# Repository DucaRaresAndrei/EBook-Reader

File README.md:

**Duca Andrei-Rares - 331CA**

# OpenBook - E-Book Reader

## Diagrama bloc

## Descrierea functionalitatilor hardware

Proiectul OpenBook Reader se bazeaza pe un microcontroller ESP32-C6 care gestioneaza comunicatia si controlul mai multor componente si senzori. Sistemul este alimentat fie printr-un port USB-C, fie printr-o baterie Li-Po reincarcabila, gestionata de un modul de incarcare MCP73831. Tensiunea de 3.3V necesara majoritatii componentelor este furnizata de un regulator LDO.

### Module si componente principale:

- **ESP32-C6 (modul principal)**  
  Controleaza comunicatia cu toate modulele periferice prin protocoale SPI, I2C, UART si GPIO.

- **Modul de incarcare MCP73831 + baterie Li-Po**  
  Incarca acumulatorul si permite alimentarea portabila a dispozitivului.

- **LDO Voltage Regulator (XC6220A331MR-G)**  
  Stabilizeaza tensiunea la 3.3V pentru alimentarea componentelor sensibile.

- **E-Ink Display 1.5" (EPD)**  
  Afiseaza continutul static intr-un mod eficient energetic. Este controlat prin interfata SPI.

- **SD Card**  
  Utilizat pentru stocarea fisierelor, accesat prin SPI.

- **External NOR Flash 64MB (W25Q512JVEIQ)**  
  Memorie externa conectata prin SPI pentru stocare suplimentara.

- **RTC Module DS3231SN**  
  Asigura un ceas de timp real precis, comunicand prin I2C.

- **Sensor BME688**  
  Senzor ambiental (temperatura, umiditate, presiune, calitate aer) conectat prin I2C.

- **Butoane fizice (RESET, BOOT, CHANGE)**  
  Conectate direct la GPIO pentru interactiune manuala si control.

### Specificatii si interfete utilizate:

| Componenta             | Interfata       | Tensiune  | Detalii                                    |
|------------------------|-----------------|-----------|---------------------------------------------|
| E-Ink Display          | SPI             | 3.3V      | 1.5", 200x200px                             |
| SD Card                | SPI             | 3.3V      | Card microSD pentru stocare externa         |
| External NOR Flash     | SPI             | 3.3V      | Memorie Flash 64MB                          |
| RTC DS3231SN           | I2C             | 3.3V      | Ceas cu cristal integrat                    |
| Senzor BME688          | I2C             | 3.3V      | Temperatura, presiune, gaz, umiditate       |
| Butoane                | GPIO            | -         | RESET, BOOT, CHANGE                         |

### Aspecte legate de consumul de energie:

E-Ink-ul si RTC-ul sunt componente cu consum foarte redus, ceea ce permite un timp indelungat de utilizare pe baterie. Comutarea modulelor periferice se face prin pinii GPIO pentru a permite dezactivarea lor in modul deep sleep. Consumul estimat in idle este de aproximativ 0.5 mA, iar in activitate de pana la 150 mA (in functie de sarcina EPD si activitatea ESP32).

## Pini ESP32-C6

| Pin ESP32-C6 | Functie            | Componenta          | Justificare                                                                 |
|--------------|--------------------|----------------------|------------------------------------------------------------------------------|
| EN           | RESET              | Buton Reset          | Reset hardware general pentru microcontroller                               |
| IO0          | INT RTC            | RTC DS3231SN         | Semnal de wake-up de la RTC                                                 |
| IO1          | 32KHZ              | RTC DS3231SN         | Iesire frecventa 32kHz din RTC                                               |
| IO2          | MISO               | SPI (Flash, SD)      | Linie de date SPI pentru citire (shared)                                    |
| IO3          | EPD_BUSY           | E-Ink Display         | Citire stare de ocupare a display-ului                                      |
| IO4          | SS_SD              | SD Card              | Chip Select pentru cardul microSD                                           |
| IO5          | EPD_DC             | E-Ink Display         | Selectie Comanda/Data pentru e-paper                                        |
| IO6          | SCK                | SPI Bus              | Clock SPI comun pentru SD, Flash, EPD                                       |
| IO7          | MOSI               | SPI Bus              | Linie de date SPI pentru scriere (shared)                                   |
| IO8          | IO/BOOT            | Buton Boot           | Intrare in modul programare (Flash Mode)                                    |
| IO9          | -                  | -                    | Pin neutilizat                                                              |
| IO10         | -                  | -                    | Pin neutilizat                                                              |
| IO11         | FLASH_CS           | NOR Flash            | Chip Select dedicat pentru memoria externa                                  |
| IO12         | USB D-             | USB-C                | Linie USB pentru comunicare si alimentare                                   |
| IO13         | USB D+             | USB-C                | Linie USB pentru comunicare si alimentare                                   |
| IO15         | IO/CHANGE          | Buton CHANGE         | Buton pentru schimbarea modului de afisare sau functionalitate              |
| IO16         | TX (UART0)         | Debug Serial         | Transmitere date catre monitor serial                                       |
| IO17         | RX (UART0)         | Debug Serial         | Receptie date de la monitor serial                                          |
| IO18         | RTC_RST            | RTC DS3231SN         | Reset software pentru RTC                                                   |
| IO19         | I2C_PW             | BME688               | Control alimentare senzor prin tranzistor                                   |
| IO20         | EPD_3V3_C          | E-Ink Display         | Activare alimentare 3.3V pentru e-paper                                     |
| IO21         | SDA                | I2C (RTC, BME688)    | Linia de date I2C partajata                                                 |
| IO22         | SCL                | I2C (RTC, BME688)    | Linia de ceas I2C partajata                                                 |
| IO23         | EPD_RST            | E-Ink Display         | Reset hardware pentru display                                               |

## Bill Of Materials

| Componenta | Link de cumparare | Datasheet |
|-----------|--------------|-----------|
| ESP32-C6-WROOM-1-N8 | [Model](https://www.snapeda.com/parts/ESP32-C6-WROOM-1-N8/Espressif+Systems/view-part/?ref=eda) | [Datasheet](//efaidnbmnnnibpcajpcglclefindmkaj/https://www.mouser.com/catalog/specsheets/Espressif_ESP32_C6_WROOM_1%20_Datasheet_V0.1_PRELIMINARY_en.pdf?srsltid=AfmBOooHQKNitqODRaaPjoZInfWKTacDER1t5uRK6sKqT13TrzvVo_B7) |
| Si1308EDL-T1-GE3 | [Model](https://componentsearchengine.com/part-view/SI1308EDL-T1-GE3/Vishay) | [Datasheet](https://www.alldatasheet.com/view.jsp?Searchword=Si1308edl&gad_source=1&gbraid=0AAAAADcdDU-px713ONYSnQ2O-gcwqYcFq&gclid=Cj0KCQjwqcO_BhDaARIsACz62vN_Nz3MJOc6J_03gnVBm7aSqC8v9wyP0VD-iRKP-gFrYgdhLi99I14aAlVJEALw_wcB) |
| KP-1608SURCK | [Model](https://www.snapeda.com/parts/KP-1608SURCK/Kingbright/view-part/?ref=search&t=LED%200603) | [Datasheet](//efaidnbmnnnibpcajpcglclefindmkaj/https://media.elv.com/file/107153_led_surck1608_data.pdf) |
| R0402 | [Model](https://componentsearchengine.com/part-view/R0402%201%25%20100%20K%20(RC0402FR-07100KL)/YAGEO) | [Datasheet](//efaidnbmnnnibpcajpcglclefindmkaj/https://www.resistor.com/assets/pdf/0402tstd.pdf) |
| DS3231SN# | [Model](https://www.snapeda.com/parts/DS3231SN%23/Analog+Devices/view-part/?ref=eda) | [Datasheet](https://www.alldatasheet.com/view.jsp?Searchword=Ds3231sn%20datasheet&gad_source=1&gbraid=0AAAAADcdDU-Gy9URfMxGmqiPg7ci5L3wR&gclid=Cj0KCQjwqcO_BhDaARIsACz62vMkK3ETSnW2w7mo0Fa-wgWJGn89AxWCyIND6k5X8MmoPl6hv6VWwT8aAiS-EALw_wcB) |
| PGB1010603MR | [Model](https://www.snapeda.com/parts/PGB1010603MR/Littelfuse/view-part/?ref=eda) | [Datasheet](https://www.alldatasheet.com/view.jsp?Searchword=Pgb1010603mr&gad_source=1&gbraid=0AAAAADcdDU8aYfZtfJfdZ9I5j6RwZ_cbA&gclid=Cj0KCQjwqcO_BhDaARIsACz62vOPBOBe0eOh5gDUFkkKl4JBcbmoFZYtJ8BOnbaWqr_BuUCcVWvbutAaAmGkEALw_wcB) |
| USBLC6-2SC6Y | [Model](https://www.snapeda.com/parts/USBLC6-2SC6Y/STMicroelectronics/view-part/?ref=eda) | [Datasheet](https://www.digikey.com/en/htmldatasheets/production/1375342/0/0/1/usblc6-2sc6y) |
| USB4110-GF-A | [Model](https://componentsearchengine.com/part-view/USB4110-GF-A/GCT%20(GLOBAL%20CONNECTOR%20TECHNOLOGY)) | [Datasheet](//efaidnbmnnnibpcajpcglclefindmkaj/https://gct.co/files/drawings/usb4110.pdf) |
| CPH3225A | [Model](https://www.snapeda.com/parts/CPH3225A/Seiko+Instruments/view-part/?ref=eda) | [Datasheet](https://octopart.com/datasheet/cph3225a-seiko-25340571) |
| Adafruit | [Model](https://eu.mouser.com/ProductDetail/Adafruit/4208?qs=PzGy0jfpSMtbScLbr0L5dw%3D%3D) | [Datasheet](https://www.arrow.com/en/manufacturers/adafruit-industries/datasheets) |
| SD0805S020S1R0 | [Model](https://ro.mouser.com/ProductDetail/KYOCERA-AVX/SD0805S020S1R0?qs=jCA%252BPfw4LHbpkAoSnwrdjw%3D%3D) | [Datasheet](https://www.alldatasheet.com/view.jsp?Searchword=SD0805S&sField=2) |
| W25Q512JVEIQ | [Model](https://www.snapeda.com/parts/ESP32-C6-WROOM-1-N8/Espressif+Systems/view-part/?ref=eda) | [Datasheet](//efaidnbmnnnibpcajpcglclefindmkaj/https://www.mouser.com/datasheet/2/949/W25Q512JV_SPI_RevB_06252019_KMS-2487502.pdf?srsltid=AfmBOoquExqDVgxEELF9CzuOGxHos0CD1nQDROHD6Eebdm2foNzqozqU) |
| EVQPUJ02K | [Model](https://industry.panasonic.com/global/en/products/control/switch/light-touch/number/evqpuj02k) | [Datasheet](https://www.lcsc.com/datasheet/lcsc_datasheet_2201121800_PANASONIC-EVQPUJ02K_C2936858.pdf) |
| XC6220A331MR-G | [Model](https://componentsearchengine.com/part-view/XC6220A331MR-G/Torex) | [Datasheet](https://www.alldatasheet.com/view.jsp?Searchword=Xc6220&gad_source=1&gbraid=0AAAAADcdDU8aYfZtfJfdZ9I5j6RwZ_cbA&gclid=Cj0KCQjwqcO_BhDaARIsACz62vPS06NB6tLgniZzfaVpKNu1m811BNk6AEPfg4DbP6f5S8QWA_pW_UQaAv-0EALw_wcB) |
| Bobina | [Model](https://store.comet.srl.ro/Catalogue/Product/43497/) | [Datasheet](https://www.scribd.com/document/814581278/Datasheet-Bobina) |
| MAX17048G+T10 | [Model](https://www.snapeda.com/parts/MAX17048G+T10/Analog+Devices/view-part/?ref=eda) | [Datasheet](https://www.alldatasheet.com/view.jsp?Searchword=Max17048&gad_source=1&gbraid=0AAAAADcdDU8aYfZtfJfdZ9I5j6RwZ_cbA&gclid=Cj0KCQjwqcO_BhDaARIsACz62vNa9xrVfzjCjADRwXD0RBbo4Nret3ywwteDGLJKZui8ZL8KdVlTE7caAvQxEALw_wcB) |
| SMD Solder | [Model](https://grabcad.com/library/solder-jumpers-1) | [Datasheet]() |
| BUTTON | [Model](https://industry.panasonic.com/global/en/products/control/switch/light-touch/number/evqpuj02k) | [Datasheet](https://www.lcsc.com/datasheet/lcsc_datasheet_2201121800_PANASONIC-EVQPUJ02K_C2936858.pdf) |
| BME680 | [Model](https://www.snapeda.com/parts/BME680/Bosch/view-part/?welcome=home) | [Datasheet](//efaidnbmnnnibpcajpcglclefindmkaj/https://www.bosch-sensortec.com/media/boschsensortec/downloads/datasheets/bst-bme680-ds001.pdf) |
| PFMF | [Model](https://www.mouser.co.uk/ProductDetail/EPCOS-TDK/B72520T0350K062?qs=dEfas%2FXlABIszF52uu7vrg%3D%3D) | [Datasheet](https://ro.mouser.com/c/ds/circuit-protection/thermistors/resettable-fuses-pptc/?m=Schurter&series=PFMF) |
| DMG2305UX-7 | [Model](https://componentsearchengine.com/part-view/DMG2305UX-7/Diodes%20Incorporated) | [Datasheet](//efaidnbmnnnibpcajpcglclefindmkaj/https://www.mouser.com/datasheet/2/115/DMG2305UX-266242.pdf?srsltid=AfmBOop22k34YTJJra1xubiU6LPiN4M4JlcWbRoSNdxSGFak8uWgXPpK) |
| BD5229G-TR | [Model](https://componentsearchengine.com/part-view/BD5229G-TR/ROHM%20Semiconductor) | [Datasheet](https://www.lcsc.com/datasheet/lcsc_datasheet_2201131330_ROHM-Semicon-BD5229G-TR_C962636.pdf) |
| MCP73831T-5ACI/OT | [Model](https://www.mouser.co.uk/ProductDetail/Microchip-Technology/MCP73831T-5ACI-OT?qs=hH%252BOa0VZEiAcgAcEkuamXg%3D%3D) | [Datasheet](//efaidnbmnnnibpcajpcglclefindmkaj/https://ww1.microchip.com/downloads/en/DeviceDoc/MCP73831-Family-Data-Sheet-DS20001984H.pdf) |
| CAPACITOR | [Model](https://componentsearchengine.com/part-view/R0402%201%25%20100%20K%20(RC0402FR-07100KL)/YAGEO) | [Datasheet](//efaidnbmnnnibpcajpcglclefindmkaj/https://www.resistor.com/assets/pdf/0402tstd.pdf) |

## Etapele implementarii proiectului:

- Am realizat schematicul conform exemplului din cerinta si folosind biblioteca specificata. Am verificat cu ERC si nu am intampinat nicio eroare. Warningurile avute au fost acceptate deoarece nu reprezinta o problema pentru structura proiectului.

- Am proiectat PCb-ul, unde am respectat in clar dimensiunile date. Am pozitionat cu grija piesele, incercand sa le pozitionez ca in fisierul exemplu. Am facut rutarea, planurile de masa si am rulat cu fisierul corect de DRC. Am rezolvat erorile de air wire pe cat de mult posibil, ramanand doar una, ce am fost nevoit sa o accept.

- Am modelat piesele 3D si le-am integrat in placa. Am intampinat probleme in a gasi anumite modele 3D, ba chiar am fost nevoit sa creez singur test pad-urile.

- Am creat manual bateria si displayul, dupa masuratorile si specificatiile cerute si le-am atasat, alaturi de modelul 3d al PCB-ului, la carcasa eBook-Reader-ului.

- Am corectat erorile, iar acum proiectul poate fi complet functional.

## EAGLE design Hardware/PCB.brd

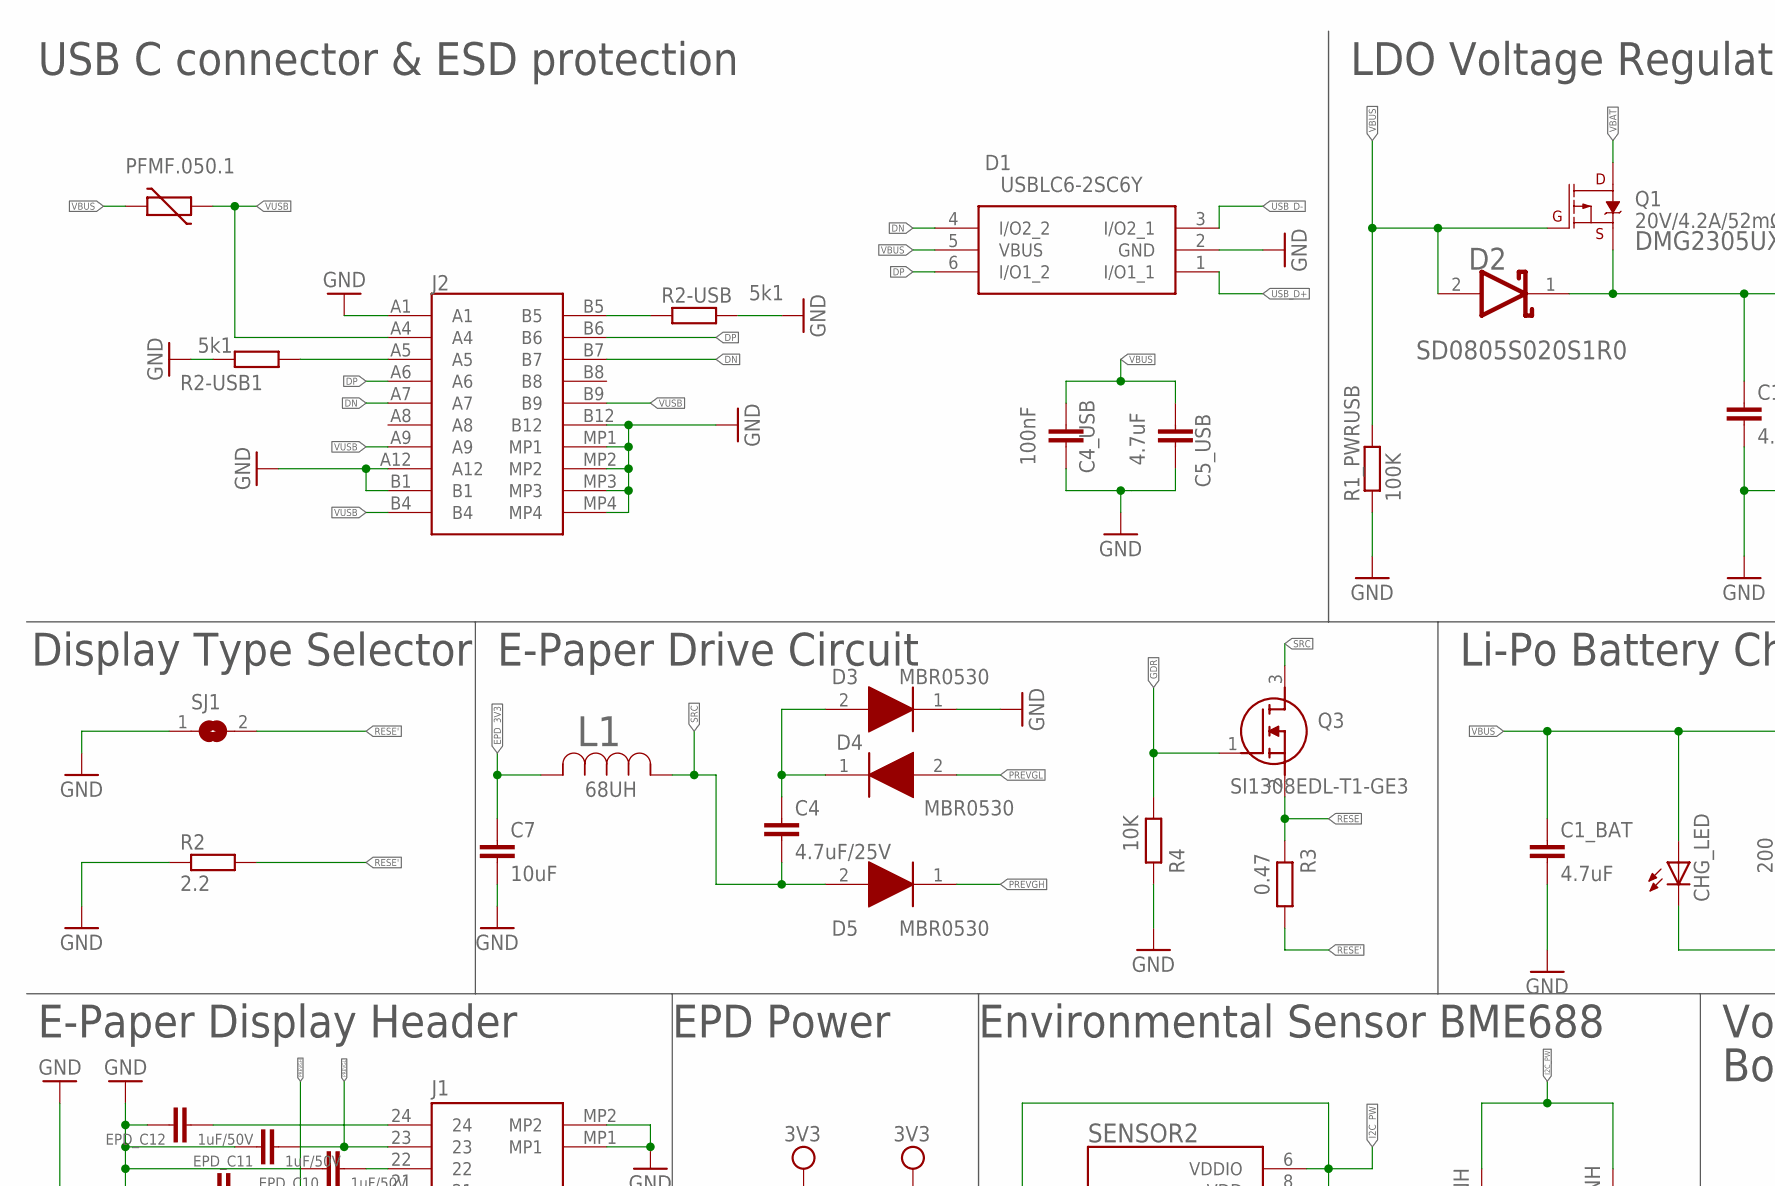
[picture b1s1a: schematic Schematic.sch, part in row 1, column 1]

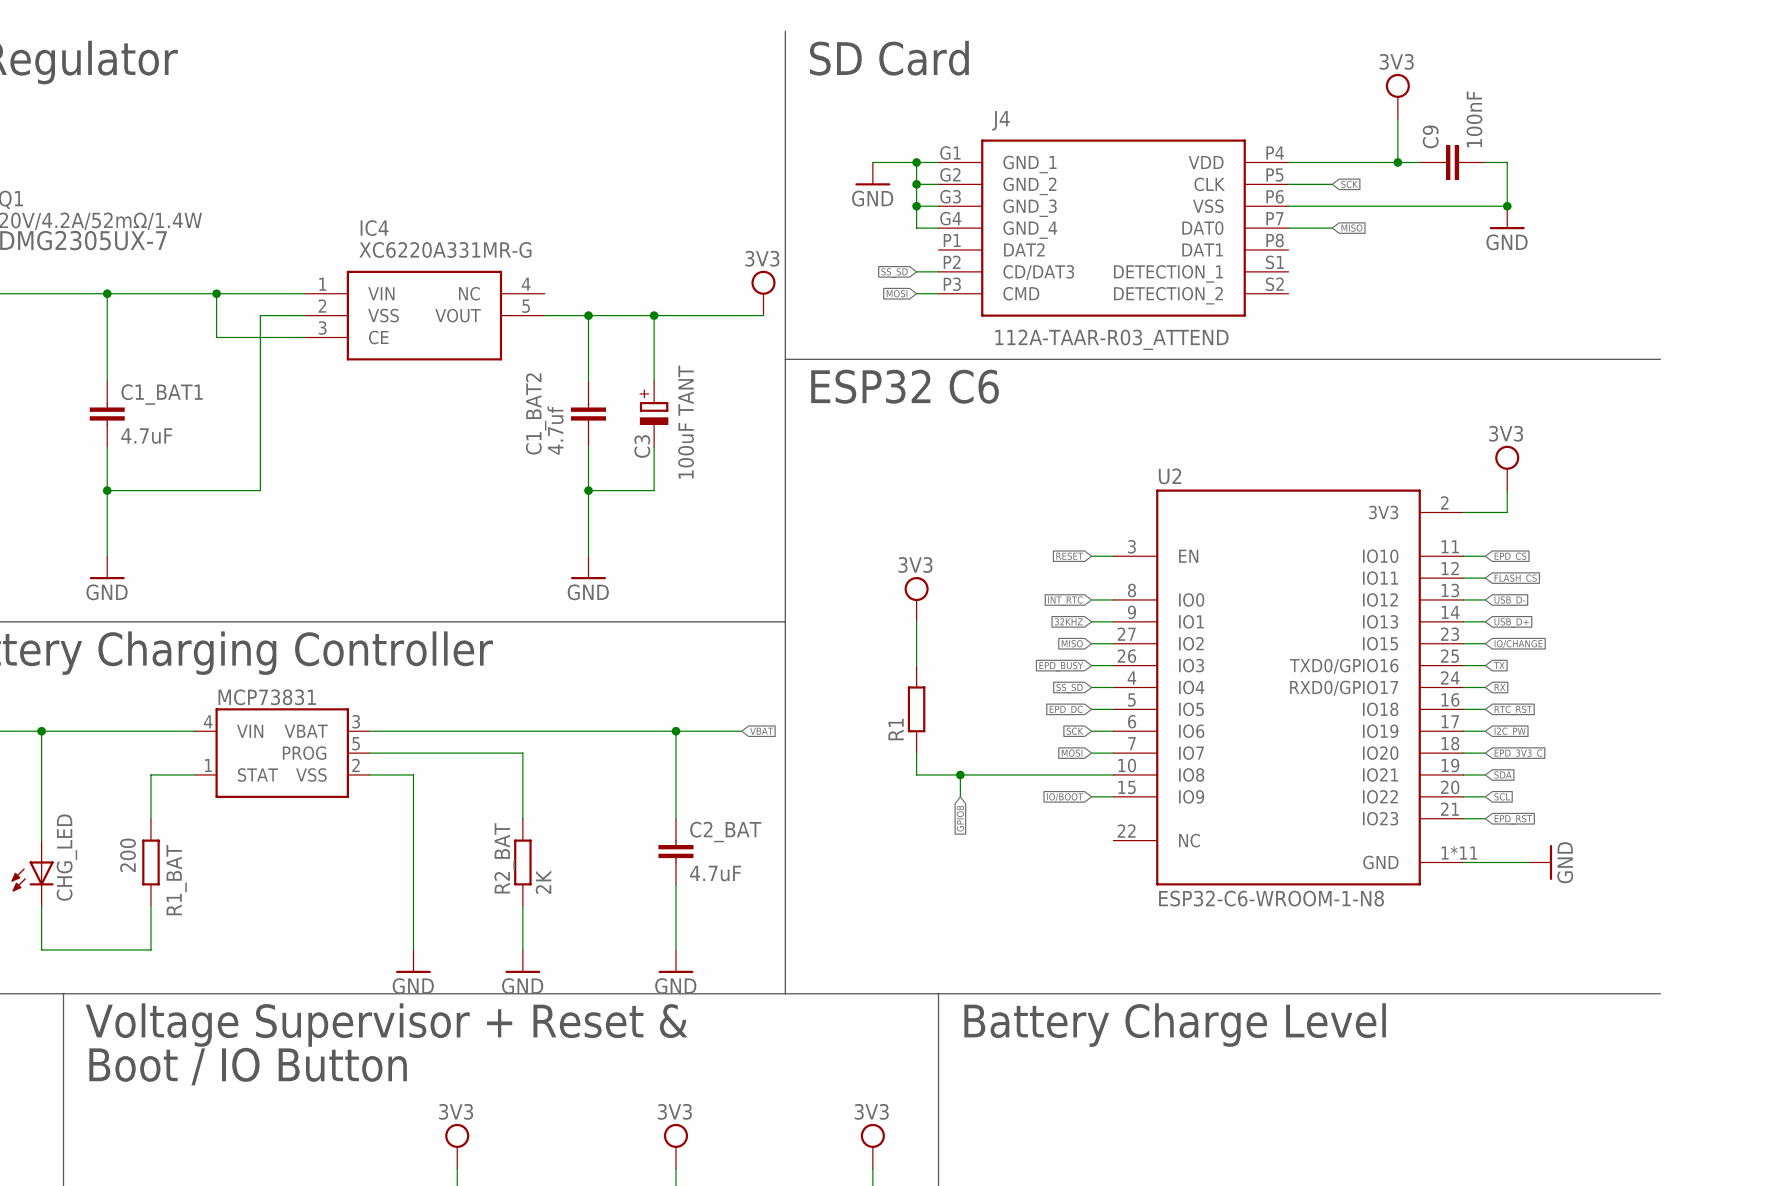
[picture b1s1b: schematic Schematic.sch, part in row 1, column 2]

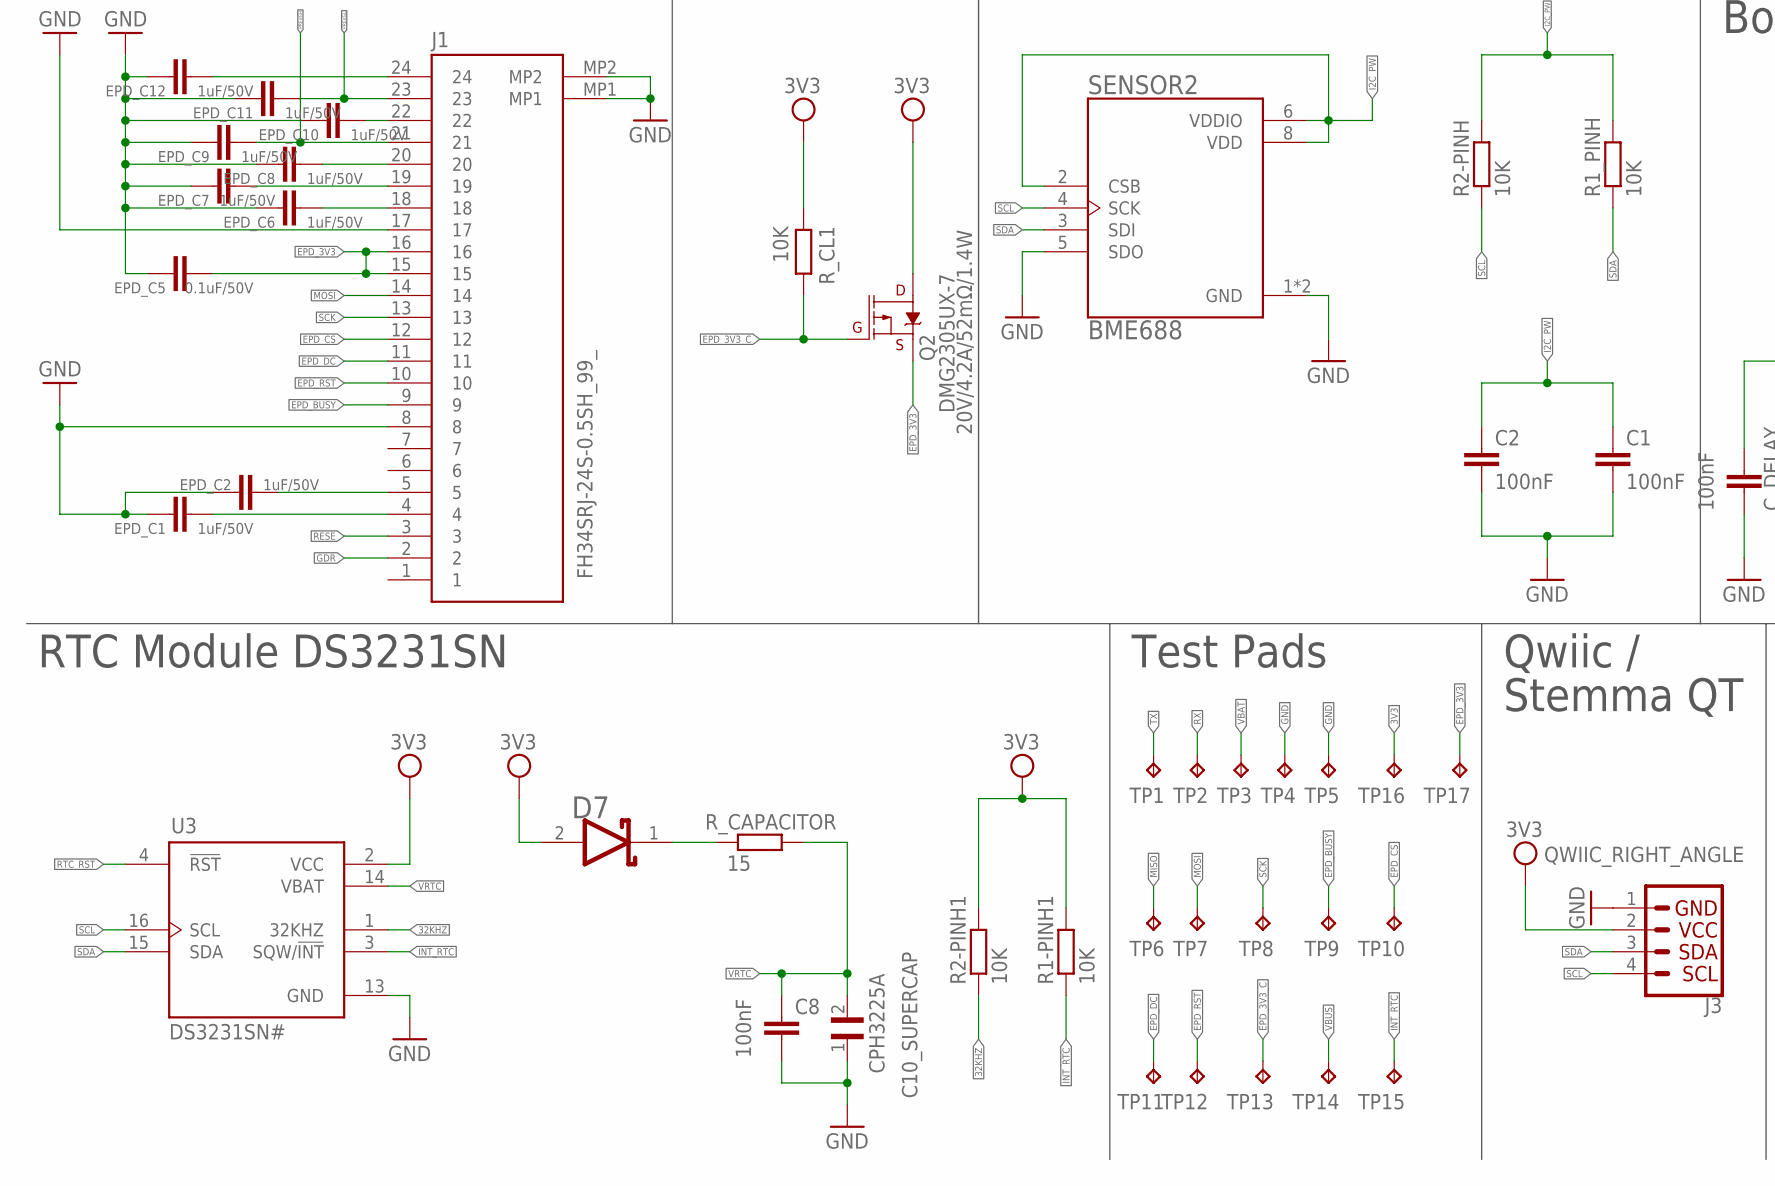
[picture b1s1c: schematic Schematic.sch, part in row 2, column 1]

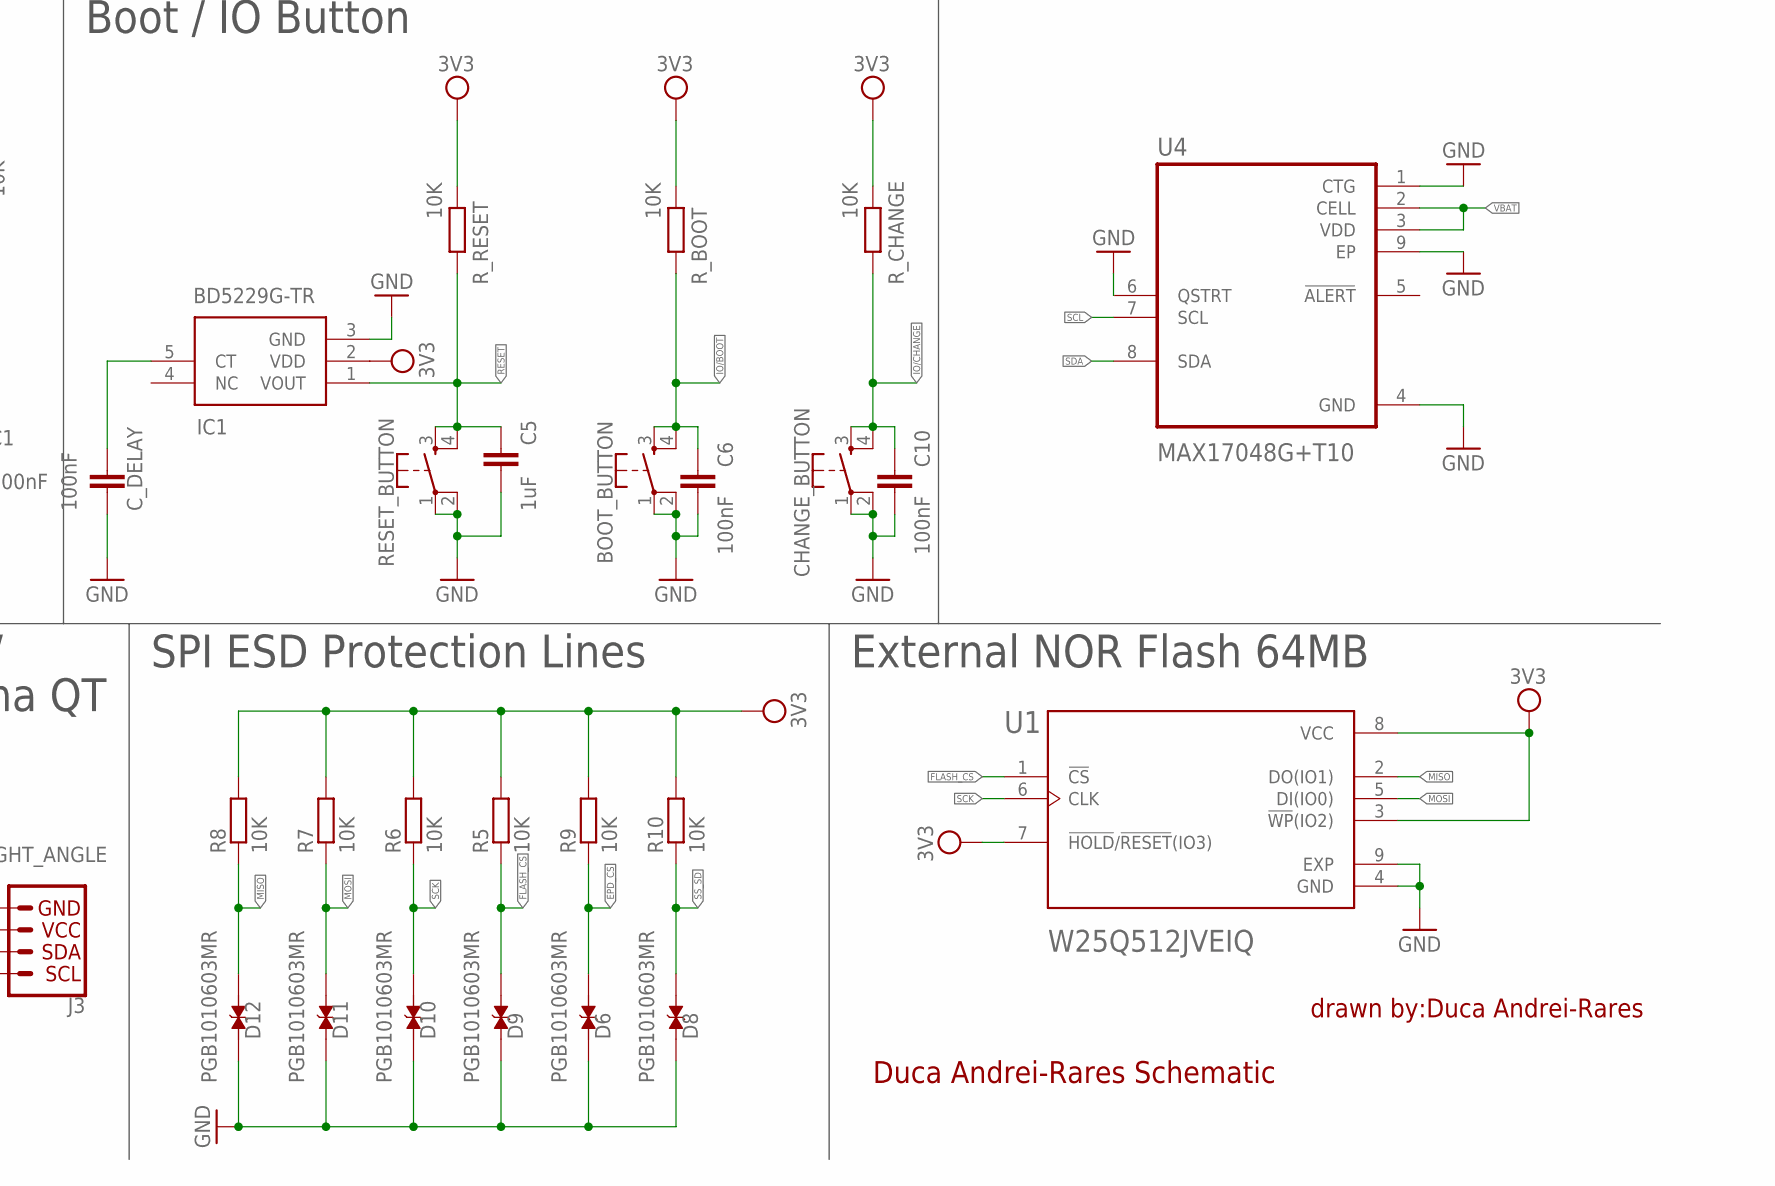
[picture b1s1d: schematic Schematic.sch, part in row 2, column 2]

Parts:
BOOT_BUTTON: BUTTON_CUSYOMV1; MYBUTTON
C1, C2, C4_USB, C6, C8, C9, C10: 100nF; EAGLE-LTSPICE_C0402
C1_BAT, C1_BAT1, C2_BAT, C5_USB: 4.7uF; EAGLE-LTSPICE_C0402
C1_BAT2: 4.7uf; EAGLE-LTSPICE_C0402
C3: 100uF TANT; RCL_CT3528
C4: 4.7uF/25V; EAGLE-LTSPICE_C0402
C5: 1uF; EAGLE-LTSPICE_C0402
C7: 10uF; EAGLE-LTSPICE_C0402
C10_SUPERCAP: CPH3225A; CAPCP3225X100N
CHANGE_BUTTON: BUTTON_CUSYOMV1; MYBUTTON
CHG_LED: ADAFRUIT_LEDCHIP-LED0603; ADAFRUIT_CHIP-LED0603
C_DELAY: 100nF; EAGLE-LTSPICE_C0402
D1: USBLC6-2SC6Y; SOT95P280X145-6N
D2: SD0805S020S1R0; ESP32_WROVER_AVX---SD0805S020S1R0_AVX_SD0805S020S1R0_0
D3, D4, D5: MBR0530; SOD3716X135N
D6, D8, D9, D10, D11, D12: PGB1010603MR; DIOC1608X36N
D7: ESP32_WROVER_AVX---SD0805S020S1R0_AVX_SD0805S020S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; ESP32_WROVER_AVX---SD0805S020S1R0_AVX_SD0805S020S1R0_0
EPD_C1, EPD_C2, EPD_C6, EPD_C7, EPD_C8, EPD_C9, EPD_C10, EPD_C11, EPD_C12: 1uF/50V; EAGLE-LTSPICE_C0402
EPD_C5: 0.1uF/50V; EAGLE-LTSPICE_C0402
IC1: BD5229G-TR; SOT95P280X125-5N
IC4: XC6220A331MR-G; SOT95P280X120-5N
J1: FH34SRJ-24S-0.5SH_99_; FH34SRJ24S05SH99
J2: SAMACSYS_PARTS_USB4110-GF-A; SAMACSYS_PARTS_USB4110GFA
J3: QWIIC_RIGHT_ANGLE; JST04_1MM_RA
J4: 112A-TAAR-R03_ATTEND; 112ATAARR03ATTEND
L1: 744043680IND_4828-WE-TPC_WRE; IND_4828-WE-TPC_WRE
MCP73831: ESP32_WROVER_SPARKFUN-IC-POWER_MCP73831; ESP32_WROVER_SPARKFUN-IC-POWER_SOT23-5
PFMF.050.1: ESP32C6_VARISTORCN1812; ESP32C6_VARISTOR_CT/CN1812
Q1, Q2: 20V/4.2A/52mΩ/1.4W; ESP32_WROVER_SPARKFUN-DISCRETESEMI_SOT23-3
Q3: SI1308EDL-T1-GE3; SOT65P210X110-3N
R1: ESP32_WROVER_EAGLE-LTSPICE_RR0402; ESP32_WROVER_EAGLE-LTSPICE_R0402
R1-PINH1, R1_PINH, R2-PINH, R2-PINH1, R4, R5, R6, R7, R8, R9, R10: 10K; ESP32_WROVER_EAGLE-LTSPICE_R0402
R1_BAT: 200; ESP32_WROVER_EAGLE-LTSPICE_R0402
R1_PWRUSB: 100K; ESP32_WROVER_EAGLE-LTSPICE_R0402
R2: 2.2; ESP32_WROVER_EAGLE-LTSPICE_R0402
R2-USB, R2-USB1: 5k1; ESP32_WROVER_EAGLE-LTSPICE_R0402
R2_BAT: 2K; ESP32_WROVER_EAGLE-LTSPICE_R0402
R3: 0.47; ESP32_WROVER_EAGLE-LTSPICE_R0402
RESET_BUTTON: BUTTON_CUSYOMV1; MYBUTTON
R_BOOT: 10K; ESP32_WROVER_EAGLE-LTSPICE_R0402
R_CAPACITOR: 15; ESP32_WROVER_EAGLE-LTSPICE_R0402
R_CHANGE: 10K; ESP32_WROVER_EAGLE-LTSPICE_R0402
R_CL1: 10K; ESP32_WROVER_EAGLE-LTSPICE_R0402
R_RESET: 10K; ESP32_WROVER_EAGLE-LTSPICE_R0402
SENSOR2: ESP32_WROVER_BME680_BME680; ESP32_WROVER_BME680_PSON80P300X300X100-8N
SJ1: SJ
TP1, TP2, TP3, TP4, TP5, TP6, TP7, TP8, TP9, TP10, TP11, TP12, TP13, TP14, TP15, TP16, TP17: TPTP20R; TP20R
U1: W25Q512JVEIQ; SON127P600X800X80-9N
U2: ESP32-C6-WROOM-1-N8; XCVR_ESP32-C6-WROOM-1-N8
U3: DS3231SN#; SOIC127P1032X265-16N
U4: MAX17048G+T10; SON50P200X200X80-9N

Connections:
3V3: C1_BAT2.1, C3.+, C9.1, D7.2 (ANODE), IC1.2 (VDD), IC4.5 (VOUT), J3.2, J4.P4 (VDD), Q2.3 (D), R1.2, R1-PINH1.2, R2-PINH1.2, R5.2, R6.2, R7.2, R8.2, R9.2, R10.2, R_BOOT.2, R_CHANGE.2, R_CL1.2, R_RESET.2, TP16.TP, U1.3 (!WP!(IO2)), U1.7 (!HOLD!/!RESET!(IO3)), U1.8 (VCC), U2.2 (3V3), U3.2 (VCC)
32KHZ: R2-PINH1.1, U2.9 (IO1), U3.1 (32KHZ)
DN: D1.4 (I/O2_2), J2.A7, J2.B7
DP: D1.6 (I/O1_2), J2.A6, J2.B6
EPD_3V3: C7.1, EPD_C5.2, J1.15, J1.16, L1.2, Q2.2 (S), TP17.TP
EPD_3V3_C: Q2.1 (G), R_CL1.1, TP13.TP, U2.18 (IO20)
EPD_BUSY: J1.9, TP9.TP, U2.26 (IO3)
EPD_CS: D6.2, J1.12, R9.1, TP10.TP, U2.11 (IO10)
EPD_DC: J1.11, TP11.TP, U2.5 (IO5)
EPD_RST: J1.10, TP12.TP, U2.21 (IO23)
FLASH_CS: D9.2, R5.1, U1.1 (!CS), U2.12 (IO11)
GDR: J1.2, Q3.1 (G), R4.2
GND: BOOT_BUTTON.1, BOOT_BUTTON.2, C1.2, C1_BAT.2, C1_BAT1.2, C1_BAT2.2, C2.2, C2_BAT.2, C3.-, C4_USB.2, C5.2, C5_USB.2, C6.2, C7.2, C8.2, C9.2, C10.2, C10_SUPERCAP.1, CHANGE_BUTTON.1, CHANGE_BUTTON.2, C_DELAY.2, D1.2 (GND), D3.1 (K), D6.1, D8.1, D9.1, D10.1, D11.1, D12.1, EPD_C1.1, EPD_C2.1, EPD_C5.1, EPD_C6.1, EPD_C7.1, EPD_C8.1, EPD_C9.1, EPD_C10.1, EPD_C11.1, EPD_C12.1, IC1.3 (GND), IC4.2 (VSS), J1.8, J1.17, J1.MP1, J1.MP2, J2.A1, J2.A12, J2.B1, J2.B12, J2.MP1, J2.MP2, J2.MP3, J2.MP4, J3.1, J4.G1 (GND_1), J4.G2 (GND_2), J4.G3 (GND_3), J4.G4 (GND_4), J4.P6 (VSS), MCP73831.2 (VSS), R1_PWRUSB.1, R2.1, R2-USB.2, R2-USB1.1, R2_BAT.1, R4.1, RESET_BUTTON.1, RESET_BUTTON.2, SENSOR2.1 (GND), SENSOR2.5 (SDO), SENSOR2.7 (GND), SJ1.1, TP4.TP, TP5.TP, U1.4 (GND), U1.9 (EXP), U2.1 (GND), U2.28 (GND), U2.29_1 (GND), U2.29_2 (GND), U2.29_3 (GND), U2.29_4 (GND), U2.29_5 (GND), U2.29_6 (GND), U2.29_7 (GND), U2.29_8 (GND), U2.29_9 (GND), U3.13 (GND), U4.1 (CTG), U4.4 (GND), U4.6 (QSTRT), U4.9 (EP)
GPIO8: R1.1, U2.10 (IO8)
I2C_PW: C1.1, C2.1, R1_PINH.2, R2-PINH.2, SENSOR2.2 (CSB), SENSOR2.6 (VDDIO), SENSOR2.8 (VDD), U2.17 (IO19)
INT_RTC: R1-PINH1.1, TP15.TP, U2.8 (IO0), U3.3 (SQW/!INT)
IO/BOOT: BOOT_BUTTON.3, BOOT_BUTTON.4, C6.1, R_BOOT.1, U2.15 (IO9)
IO/CHANGE: C10.1, CHANGE_BUTTON.3, CHANGE_BUTTON.4, R_CHANGE.1, U2.23 (IO15)
MISO: D12.2, J4.P7 (DAT0), R8.1, TP6.TP, U1.2 (DO(IO1)), U2.27 (IO2)
MOSI: D11.2, J1.14, J4.P3 (CMD), R7.1, TP7.TP, U1.5 (DI(IO0)), U2.7 (IO7)
unnamed: J2.B5, R2-USB.1
unnamed: C1_BAT1.1, D2.1 (CATHODE), IC4.1 (VIN), IC4.3 (CE), Q1.2 (S)
unnamed: CHG_LED.C, R1_BAT.1
unnamed: MCP73831.5 (PROG), R2_BAT.2
unnamed: C4.1, D3.2 (A), D4.1 (K)
unnamed: J2.A5, R2-USB1.2
unnamed: EPD_C1.2, J1.4
unnamed: MCP73831.1 (STAT), R1_BAT.2
unnamed: EPD_C2.2, J1.5
unnamed: C_DELAY.1, IC1.5 (CT)
unnamed: D7.1 (CATHODE), R_CAPACITOR.1
unnamed: EPD_C12.2, J1.24
unnamed: EPD_C10.2, J1.22
unnamed: EPD_C8.2, J1.20
unnamed: EPD_C7.2, J1.19
unnamed: EPD_C6.2, J1.18
PREVGH: D5.1 (K), EPD_C9.2, J1.21
PREVGL: D4.2 (A), EPD_C11.2, J1.23
RESE: J1.3, Q3.2 (S), R3.2
RESE': R2.2, R3.1, SJ1.2
RESET: C5.1, IC1.1 (VOUT), RESET_BUTTON.3, RESET_BUTTON.4, R_RESET.1, U2.3 (EN)
RTC_RST: U2.16 (IO18), U3.4 (!RST)
RX: TP2.TP, U2.24 (RXD0/GPIO17)
SCK: D10.2, J1.13, J4.P5 (CLK), R6.1, TP8.TP, U1.6 (CLK), U2.6 (IO6)
SCL: J3.4, R2-PINH.1, SENSOR2.4 (SCK), U2.20 (IO22), U3.16 (SCL), U4.7 (SCL)
SDA: J3.3, R1_PINH.1, SENSOR2.3 (SDI), U2.19 (IO21), U3.15 (SDA), U4.8 (SDA)
SRC: C4.2, D5.2 (A), L1.1, Q3.3 (D)
SS_SD: D8.2, J4.P2 (CD/DAT3), R10.1, U2.4 (IO4)
TX: TP1.TP, U2.25 (TXD0/GPIO16)
USB_D+: D1.1 (I/O1_1), U2.14 (IO13)
USB_D-: D1.3 (I/O2_1), U2.13 (IO12)
VBAT: C2_BAT.1, MCP73831.3 (VBAT), Q1.3 (D), TP3.TP, U4.2 (CELL), U4.3 (VDD)
VBUS: C1_BAT.1, C4_USB.1, C5_USB.1, CHG_LED.A, D1.5 (VBUS), D2.2 (ANODE), MCP73831.4 (VIN), PFMF.050.1.2, Q1.1 (G), R1_PWRUSB.2, TP14.TP
VRTC: C8.1, C10_SUPERCAP.2, R_CAPACITOR.2, U3.14 (VBAT)
VUSB: J2.A4, J2.A9, J2.B4, J2.B9, PFMF.050.1.1

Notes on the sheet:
LDO Voltage Regulator
USB C connector & ESD protection
SD Card
Display Type Selector
E-Paper Drive Circuit
Li-Po Battery Charging Controller
ESP32 C6
Duca Andrei-Rares Schematic
drawn by:Duca Andrei-Rares
E-Paper Display Header
EPD Power
Environmental Sensor BME688
Voltage Supervisor + Reset &
Boot / IO Button
Battery Charge Level
RTC Module DS3231SN
Test Pads
Qwiic /
Stemma QT
SPI ESD Protection Lines
External NOR Flash 64MB

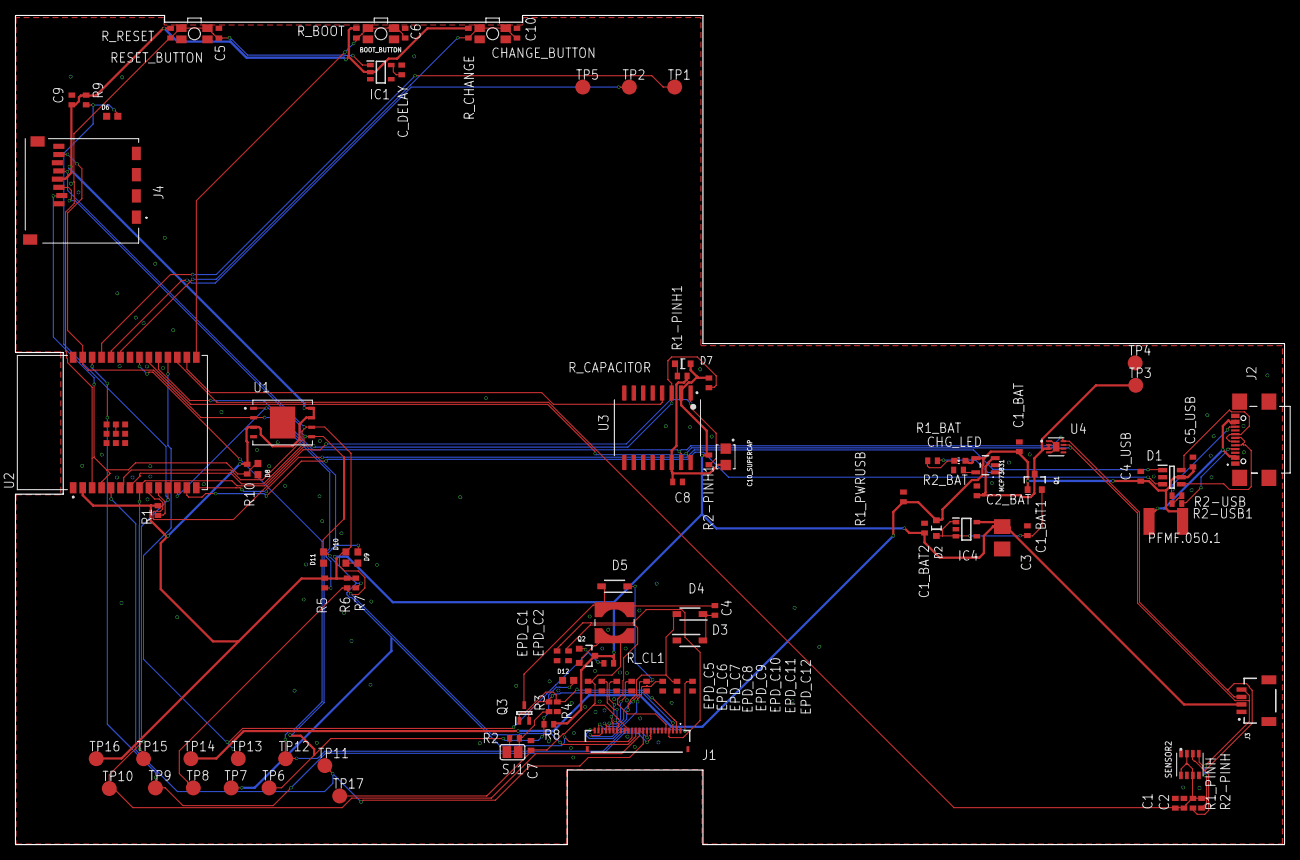
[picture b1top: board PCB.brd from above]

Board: 2 copper layers, 170.2 x 111.2 mm, 103 parts (0 on the bottom side), 55 nets.

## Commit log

2025-04-06 Added Diagram
2025-04-06 Added Diagram to README
2025-04-13 Fixed issues

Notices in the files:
parts and their libraries:
COPYRIGHT: Copyright (C) 2024 Ultra Librarian. All rights reserved.
